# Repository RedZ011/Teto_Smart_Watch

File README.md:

🕐 Teto Watch

A DIY smartwatch built from scratch on an ESP32-C3, featuring a Kasane Teto-themed OLED display, an animated background character, and Bluetooth media controls for your phone.

✨ Features

- 🕓 Live clock with date and AM/PM, with a blinking colon
- 🎵 Bluetooth media control — acts as a BLE remote for whatever music app is playing on your phone (Play/Pause, Next, Back)
- 🔘 Smart single-button input:
  - Hold ~1 second → switch between the clock screen and the music player screen
  - Hold 4 seconds → power the screen off (Teto waves "Bye!!") or back on ("Hi!!")
  - Short press while the screen is off → wake the screen
  - Multi-tap (1/2/3 taps) → Play/Pause, Next, Back inside the music player
- 👋 Bye / Hi animation: Teto waves goodbye before the screen turns off and says hi when it wakes
- 🔋 Screen-off power saving: the clock and date keep running in the background while the display, Bluetooth and CPU speed are scaled down
- 🔵 Bluetooth connection icon shown on-screen when paired
- 🖼️ Custom pixel-art animations, hand-converted to C byte arrays

📸 Photos

[Music screen] 

Bye animation :

🧰 Hardware

| Component | Notes |
|---|---|
| ESP32-C3 Super Mini | Main microcontroller — BLE only (no Classic Bluetooth) |
| SSD1306 OLED (I2C, 128x64) | Main display, address 0x3C |
| 1x push button | Handles all input — short press, long press, and multi-tap |
| LiPo battery + TP4056 charger | Optional, for portable use (planned) |

🔌 Wiring

| OLED Pin | ESP32-C3 GPIO |
|---|---|
| GND | GND |
| VCC | 3.3V |
| SDA | 8 |
| SCL | 9 |

| Other | GPIO |
|---|---|
| Button | 2 (INPUT_PULLUP, other leg to GND) |

⚠️ GPIO pin numbers can vary by board/seller — always double check your specific Super Mini's silkscreen before wiring. GPIO8 and GPIO9 are boot-related pins on the C3, so if the display acts up at power-up, move I2C to other pins and change `Wire.begin(SDA, SCL)` in main.cpp.

⚙️ How It Works

🖥️ The display
The OLED has no real "layers" — the screen buffer is cleared, everything (clock text, date, Teto sprite, icons) is drawn fresh into that single buffer in order, and then pushed to the screen in one display.display() call. This avoids flicker and keeps every element in sync.

⏱️ Timing
The main loop is built on non-blocking millis() timers. Every recurring action (clock tick, Teto's animation frame, button hold detection) just checks "has enough time passed since I last did this?" every loop cycle, so the clock, animation and button reading run independently.

The one exception is the 3-second Bye/Hi animation, which currently blocks the loop while it plays. The clock catches up on the missed seconds afterwards, so the time stays correct. Turning the animation into a non-blocking state machine is on the roadmap.

🔘 Button logic
A single button drives everything, using three techniques:

- Press-start timestamps — the time is saved at the moment the button goes down, and compared against millis() while it is still held
- Hold detection with a flag — a 4-second hold fires once per press (so the screen toggles one time instead of every loop), and the release afterwards is ignored so it doesn't also count as a short press
- Multi-tap counting — counts short presses within a rolling time window to distinguish 1 tap vs 2 vs 3, triggering Play/Next/Back once the window expires

How to actually use it:

- 🔲 Hold the button for 4 seconds on any screen → Teto says "Bye!!" and the screen turns off. Press again (or hold 4 seconds) → Teto says "Hi!!" and the screen turns back on.
- ⏳ Hold the button for about 1 second and release → switches between the clock screen and the Music Player screen.
- 🎧 Once in the Music Player, control it just like tapping the button on your earbuds/handsfree:
  - 1 tap → Play / Pause
  - 2 taps → Next
  - 3 taps → Back

🔋 Screen-off mode
The watch does not use deep sleep, so it never reboots and the clock keeps counting. When the screen turns off:

1. The Bye animation plays, then the OLED is switched off with the SSD1306_DISPLAYOFF command.
2. All drawing stops, and the main loop only runs the clock and button logic.
3. Bluetooth is disconnected and advertising is stopped (NimBLE).
4. The CPU drops from 160 MHz to 80 MHz.

Waking the watch reverses these steps. The time and date are never paused.

📶 Pairing & on-screen status icons

- To pair, look for a device named "Teto Watch" in your phone's Bluetooth settings.
- Once connected successfully, a small Bluetooth icon appears on the display.
- While music is playing, a music note icon appears on the display too.

🎵 Bluetooth media control
The ESP32-C3 advertises itself as a BLE HID keyboard, sending standard media key signals (Play, Pause, Next Track, Previous Track) that any phone recognizes system-wide — no companion app needed. The watch doesn't play audio itself; it's purely a remote control for whatever's already playing on your phone.

🧩 Code structure
The project is split across multiple files instead of one giant sketch:

- main.cpp — clock, date, button handling, power modes, top-level screen logic
- MusicPlayer.h / MusicPlayer.cpp — music menu drawing, button handling, BLE media key calls
- Teto.h / Bye.h / Bluetooth.h — pixel-art frames and icons stored as byte arrays in flash (PROGMEM)

Shared objects and variables (like the display and BLE keyboard instance) are declared extern in headers so all files can safely access the same single instance.

🚀 Setup

1. Install PlatformIO (VS Code extension)
2. Clone this repo
3. Open the folder in VS Code
4. Build and upload to your ESP32-C3 Super Mini
5. (Only once WiFi/NTP time sync is enabled) add your WiFi credentials in main.cpp, and keep them out of version control

Libraries (platformio.ini): Adafruit SSD1306, Adafruit GFX, h2zero/NimBLE-Arduino@1.4.1 and a NimBLE-based BLE Keyboard library.

🗺️ Roadmap

- [ ] Sync the time over WiFi (NTP) or add an RTC module, instead of the hard-coded start time
- [ ] Non-blocking Bye/Hi animation (state machine)
- [ ] Battery and charging module, plus a battery level icon
- [ ] Light sleep with button wake for even lower power use
- [ ] 3D-printed case and strap

🧠 Known Quirks

- BLE HID bonding can be finicky on some Android phones/versions — if pairing fails, try:
  - Clearing the Bluetooth cache on your phone
  - Using a NimBLE-based BLE Keyboard fork instead of the default Bluedroid one
- Turning Bluetooth off and on again depends on the BLE Keyboard library. If the watch stays visible while the screen is off, the library is restarting advertising when the phone disconnects.
- The ESP32-C3 is BLE only — it cannot receive/play actual audio (no Classic Bluetooth/A2DP), which is why the watch controls playback rather than outputting sound itself

🙏 Credits

- Kasane Teto — fan character, used here purely as a personal fan project
- Built with Adafruit_SSD1306 and a NimBLE-based BLE Keyboard library

📄 License

This project's code (firmware/logic) is licensed under the MIT License — see the LICENSE file for details.

⚠️ Note: This license covers the original code only. The Teto artwork/sprites used on the display are fan-created content based on Kasane Teto and are not covered by this license — they belong to their respective creators/rights holders and are used here purely as a personal, non-commercial fan project.

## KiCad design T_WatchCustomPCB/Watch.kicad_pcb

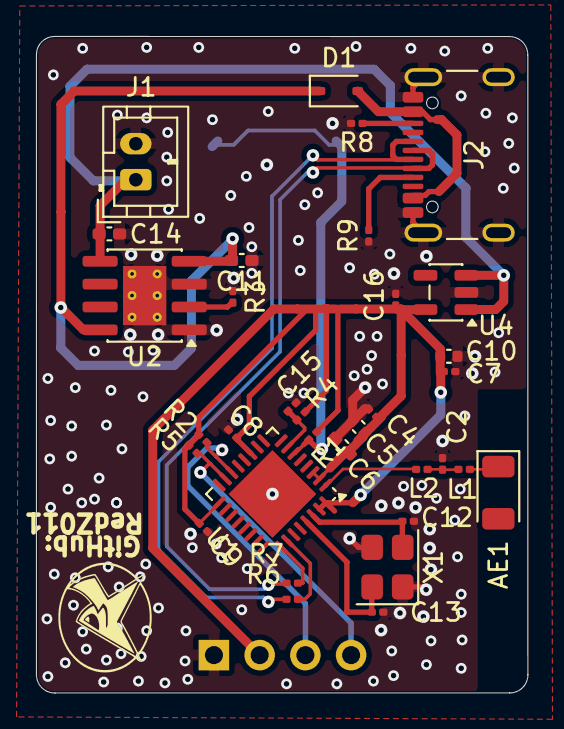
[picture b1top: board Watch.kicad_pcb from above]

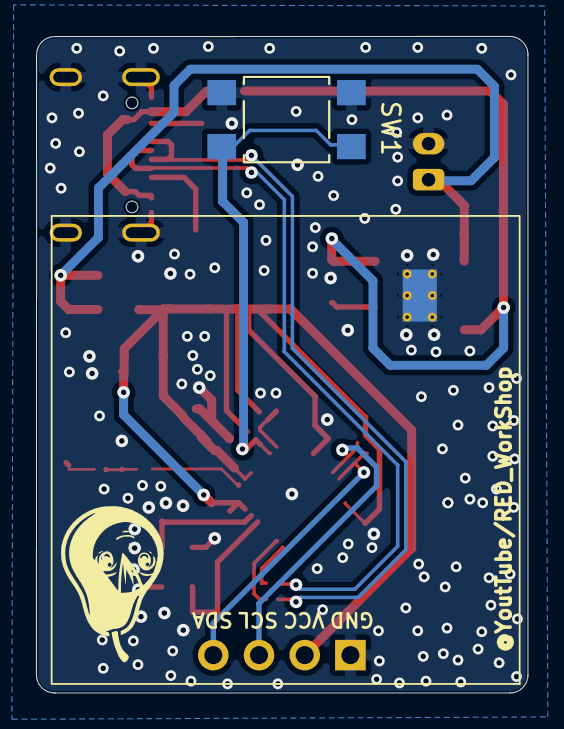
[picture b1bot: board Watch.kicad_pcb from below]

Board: 2 copper layers, 27.3 x 36.5 mm, 35 parts (2 on the bottom side), 21 nets.

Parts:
AE1: 2450AT18A100; Johanson_2450AT18x100
C2: 1pF; C_0201_0603Metric
C4, C7, C8: 100nf; C_0201_0603Metric
C5, C10: 1uF; C_0402_1005Metric
C6, C11, C14: 10uF; C_0402_1005Metric_Pad0.74x0.62mm_HandSolder
C9, C12, C13, C16: 1uF; C_0201_0603Metric
C15: 100nF; C_0201_0603Metric
D1: BAT60A; D_SOD-323
J1: BAT; JST_PH_B2B-PH-K_1x02_P2.00mm_Vertical
J2: USB C Socket; USB_C_Receptacle_GCT_USB4105-xx-A_16P_TopMnt_Horizontal
L1, L2: 2.7nH; L_0201_0603Metric
R1, R2, R4, R5: 10k; R_0201_0603Metric
R3, R8, R9: 5.1k; R_0201_0603Metric
R6, R7: 22ohm; R_0201_0603Metric
SW1: Main Button; SW_SPST_TL3305A
U1: ESP32-C3; QFN-32-1EP_5x5mm_P0.5mm_EP3.45x3.45mm
U2: TP4056-42-ESOP8; SOIC-8-1EP_3.9x4.9mm_P1.27mm_EP2.41x3.3mm_ThermalVias
U3: Adafruit_SSD1306
U4: LP5907MFX-3.3; SOT-23-5
X1: Crystal_GND24; Crystal_SMD_3225-4Pin_3.2x2.5mm

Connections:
+3.3V: C4.1, C5.1, C6.1, C7.1, C8.1, C9.1, C10.1, C16.1, R1.2, R2.2, R4.1, R5.2, U1.2 (VDD3P3), U1.3 (VDD3P3), U1.11 (VDD3P3_RTC), U1.17 (VDD3P3_CPU), U1.31 (VDDA), U1.32 (VDDA), U3.2 (VCC_IN), U4.5 (OUT)
/BAT+: C14.2, J1.1, U2.5 (BAT), U4.1 (IN), U4.3 (EN)
/CHIP_EN: C15.2, R4.2, U1.7 (CHIP_EN)
/D+: J2.A6 (D+), J2.B6 (D+), R6.1
/D-: J2.A7 (D-), J2.B7 (D-), R7.1
/GPIO2: R1.1, SW1.1, U1.6 (GPIO2/ADC1_CH2)
/GPIO8/PWM: R2.1, U1.14 (GPIO8), U3.3 (SCL)
/GPIO9/BOOT: R5.1, U1.15 (GPIO9/BOOT), U3.4 (SDA)
/XTAL_N: C13.1, U1.29 (XTAL_N), X1.4
/XTAL_P: C12.1, U1.30 (XTAL_P), X1.2
GND: C2.2, C4.2, C5.2, C6.2, C7.2, C8.2, C9.2, C10.2, C11.1, C12.2, C13.2, C14.1, C15.1, C16.2, J1.2, J2.A1 (GND), J2.A12 (GND), J2.B1 (GND), J2.B12 (GND), J2.SH (SHIELD), R3.2, R8.2, R9.2, SW1.2, U1.33 (GND), U2.1 (TEMP), U2.3 (GND), U2.9 (EPAD), U3.1 (GND), U4.2 (GND), X1.1, X1.3
unnamed: AE1.1 (A_1), L1.1
unnamed: C2.1, L1.2, L2.1
unnamed: D1.2 (A), J2.A4 (VBUS), J2.A9 (VBUS), J2.B4 (VBUS), J2.B9 (VBUS)
unnamed: J2.A5 (CC1), R9.1
unnamed: J2.B5 (CC2), R8.1
unnamed: R6.D+, U1.26 (GPIO19/USB_D+)
unnamed: R7.2, U1.25 (GPIO18/USB_D-)
unnamed: L2.2, U1.1 (LNA_IN)
unnamed: R3.1, U2.2 (PROG)
VSYS: C11.2, D1.1 (K), U2.4 (V_{CC}), U2.8 (CE)
